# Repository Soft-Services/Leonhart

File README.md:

# Leonhart
## Overview
Leonhart is a custom embedded Linux board based on the Texas Instruments AM6231 SoC.

The board is a smart-home gateway capable of running Linux and hosting Thread and Zigbee networks simultaneously using the Silicon Labs MGM240P radio module. The goal is to provide support for Matter-over-Thread devices while also bridging Zigbee devices into modern Matter-based ecosystems such as Google Home, Amazon Alexa, and Apple Home.

## Why This Matters
Many existing smart homes rely on Zigbee devices, while newer smart-home ecosystems are increasingly moving towards Matter and Thread. Replacing Zigbee devices to keep up with Matter-based ecosystems is wasteful, expensive and unnecessary.

Leonhart was created to support both worlds at once. Hosting a Thread network for newer Matter-over-Thread devices, while also hosting a Zigbee network and allowing for communication with legacy Zigbee devices. The long-term goal is to bridge Zigbee devices into Matter-based ecosystems, allowing older devices to remain useful alongside newer smart-home standards.

## Project Goals

The main goals of Leonhart are:
- Build a fully functional custom embedded Linux system
- Run Zigbee+Thread RCP firmware on MGM240P
- Thread Border Router functionality
- Zigbee network stack to communicate with radio
- Support multi protocol through Silicon Labs CPC
- Create a compact, local and open Linux-based alternative to separate Zigbee hubs and Thread border routers

## Current Status

Rev B is currently functional. Working features include:
- Linux boot from eMMC
- Ethernet and SSH
- USB-C powered boot
- Multiprotocol firmware flashed to MGM240P
- UART communication between Linux host and MGM240P with hardware flow control
- Silicon Labs CPC daemon communication
- OpenThread Border Router operation
- Thread and Zigbee network formation
- Automatic startup of Zigbee, OTBR and CPC services
- Matter-over-Thread device control using chip-tool
- Zigbee device control through Matter chip-tool commands using a simple FIFO-based Matter bridge

### Current Demo

Leonhart currently demonstrates Matter-over-Thread control and early Zigbee-to-Matter bridge functionality using the onboard MGM240P radio.

<br>

## Hardware Architecture

### Key Features
- TI AM6231 SoC
- 2 GB DDR4
- SiLabs MGM240P RF module
- 16 GB eMMC storage (HS200)
- Ethernet (RGMII PHY)
- 32kbit EEPROM
- USB-A host port
- USB-C power input
- SoC JTAG/MGM240P SWD TagConnect debug interfaces
- SPI and UART header pins for extra peripherals

### Hardware Block Diagram

<br>

## Hardware Revisions

### Rev A

Rev A was the initial bring-up revision. It successfully validated the core AM6231 Linux system, including PMIC rail sequencing, U-Boot over UART, DDR4 initialization, eMMC HS200 operation, EEPROM communication, USB-A, clocks, and Linux boot.

Main issues found in Rev A:
- Incorrect 5 V to 3.3 V buck converter footprint, requiring external 3.3 V injection
- USB-C power issue caused by the bodged power setup
- Ethernet PHY not operational
- Linux boot on power-up affected by bodged power sequencing
- Incorrect MGM240P UART and SWD pinout

### Rev B

Rev B fixed the major hardware issues from Rev A and is the current functional revision.

Main fixes and validated features in Rev B:
- MGM240P pinout now correct and can be flashed to via Silicon Labs J-Link debugger
- Ethernet and SSH are now operational
- Correct 5V -> 3.3V buck converter footprint
- USB-C power works without bodged power supply
- Linux boots from power up
- UART communication with hardware flow control works between the AM6231 and MGM240P

## Bring-Up Notes

Progress Update #1 

During initial bring-up, a bench PSU was used and a large current draw was observed, which was then found out to be an issue with the 5V -> 3.3V buck converter footprint.

A temporary workaround involved:
- Injecting 3.3V from wall adapter into 3.3V header pin
- Using a USB-C breakout board to power the PMIC and remaining rails via a bench PSU

This allowed for successful validation of:
- SoC boot
- DDR initialization
- eMMC communication

Linux boot strategy: USB-A -> DDR -> eMMC -> DDR -> boot

Progress Update #2
- Successfully booted Linux (Arago distribution)
- Rootfs and U-Boot files copied to eMMC
- Successfully able to boot from eMMC

Progress Update #3
- Modified prebuilt ti-am625-sk.dts file with only UART pinmux (UART5) for my custom board, and build .dtb file from that, then copied it to eMMC
- Tested UART5 communication with Sparkfun Things Matter MGM240P and saw output on SOC UART terminal

Progress Update #4
- Had issue with USB C power showing incorrect voltage for 5V rail (2.2V), so I used the bench power supply for dummy power. I have found that the bodged 3.3V injection setup causes the 2.2V at the USB C VBUS pins, which prevents USB C from sending power. Without the bodged setup (correct 5V->3.3V buck converter footprint) in the next revision, USB C power should work as intended
- Created new Rev B branch and started revisions

Progress Update #5 (Rev B)
- Confirmed gigabit Ethernet works and SSH works
- Linux able to boot from power up
- Confirmed onboard MGM240P communication and flashing works
- Confirmed UART hardware flow with MGM240P works
- Need to fix NCP and RCP firmware communication with CPC daemon

Progress Update #6 (Rev B)
- Successfully flashed Multiprotocol RCP/NCP (Thread and Zigbee) stack to MGM240P and had successful communication with host CPCD
- Successfully proved full Thread network chain (RCP(MGM) <-> (CPCD <-> OTBR)(AM6231)). Needed to rebuild TI Arago Linux image with multicast routing enabled

Progress Update #7 (Rev B)
- Made all Zigbee (zigbeed, zigbee-pty-bridge, Z3Gateway), Thread (OTBR, otbr-agent) and CPCD run on reboot, and successfully confirmed services correctly restart and devices reconnect
- Successfully proved Matter-over-Thread control with ESP32C6 running a Matter light example

The ESP32 commissions onto the Thread network through Leonhart, then registers its Matter operational service through SRP, then can be controlled from chip-tool over the LAN

Next steps
- Order more Zigbee and Matter-over-Thread and stress test the multiprotocol networking
- Begin to start/look into Zigbee -> Matter bridging

The following screenshots shows a script that displays the status' of the Zigbee and Thread networks and services:

## Hardware Photos

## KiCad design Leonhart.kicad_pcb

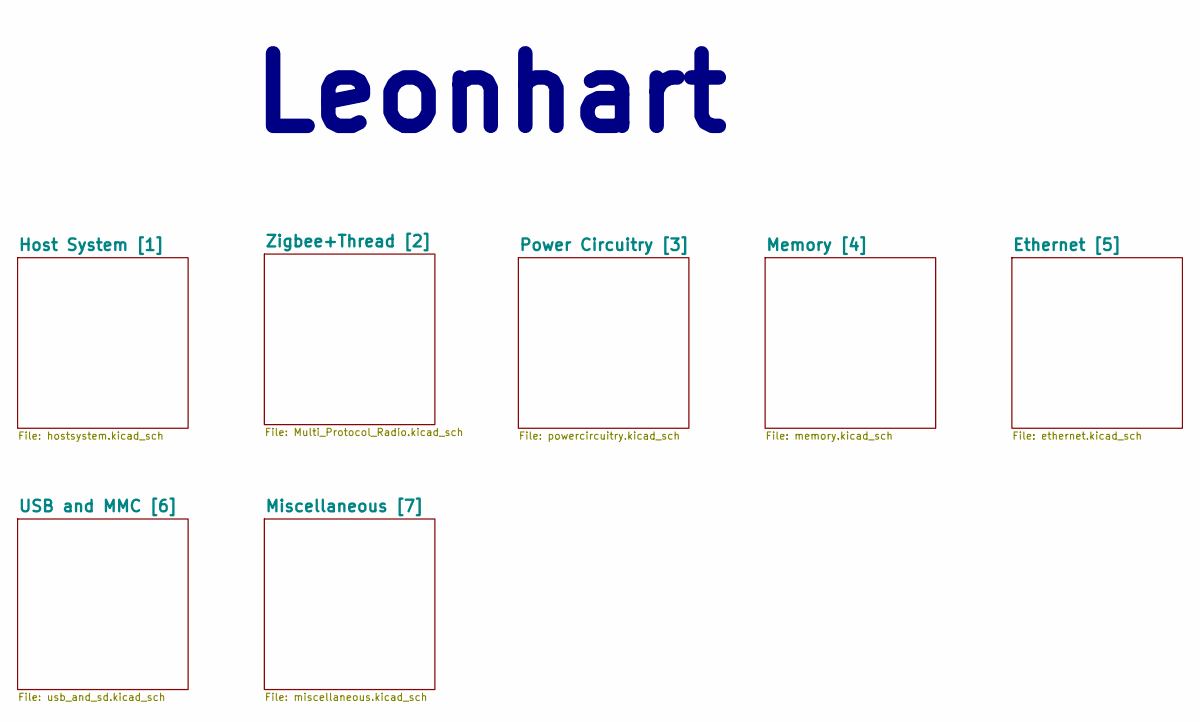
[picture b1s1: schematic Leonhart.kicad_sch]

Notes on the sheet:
Leonhart

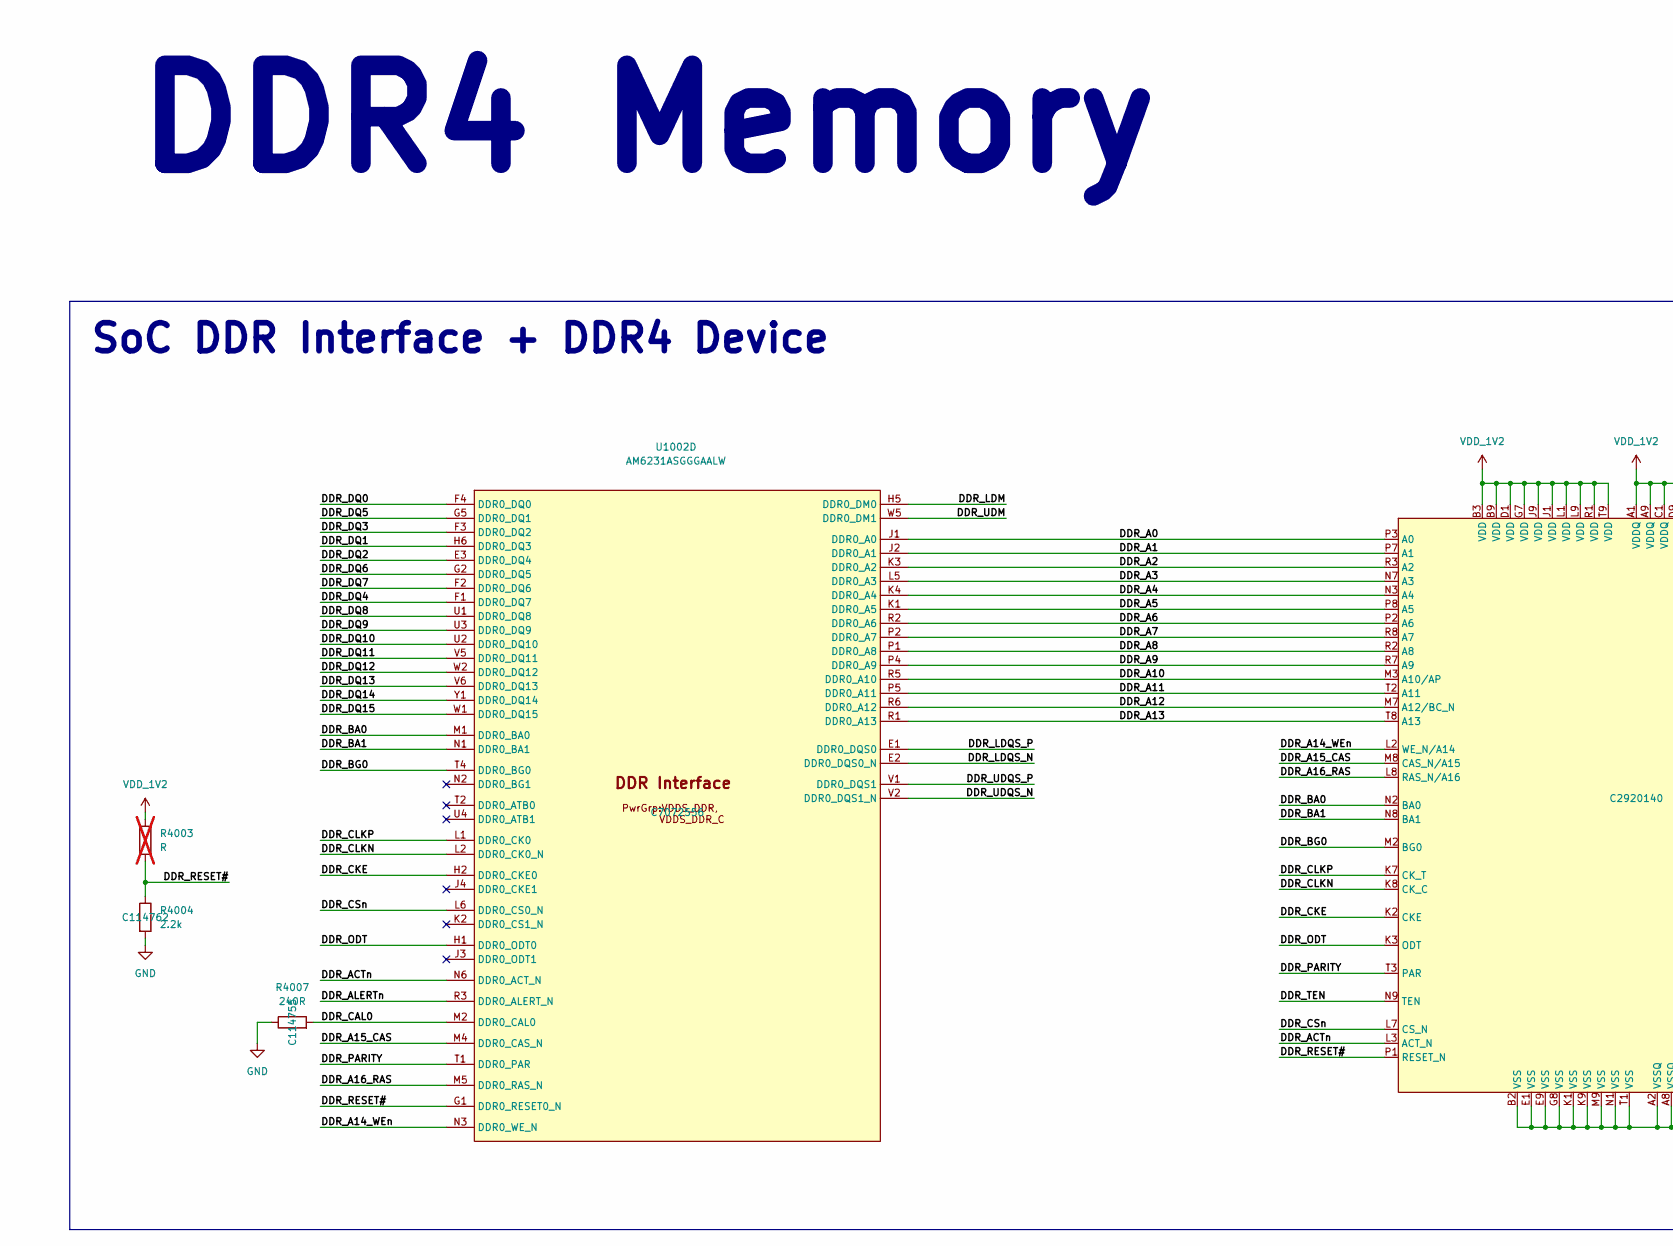
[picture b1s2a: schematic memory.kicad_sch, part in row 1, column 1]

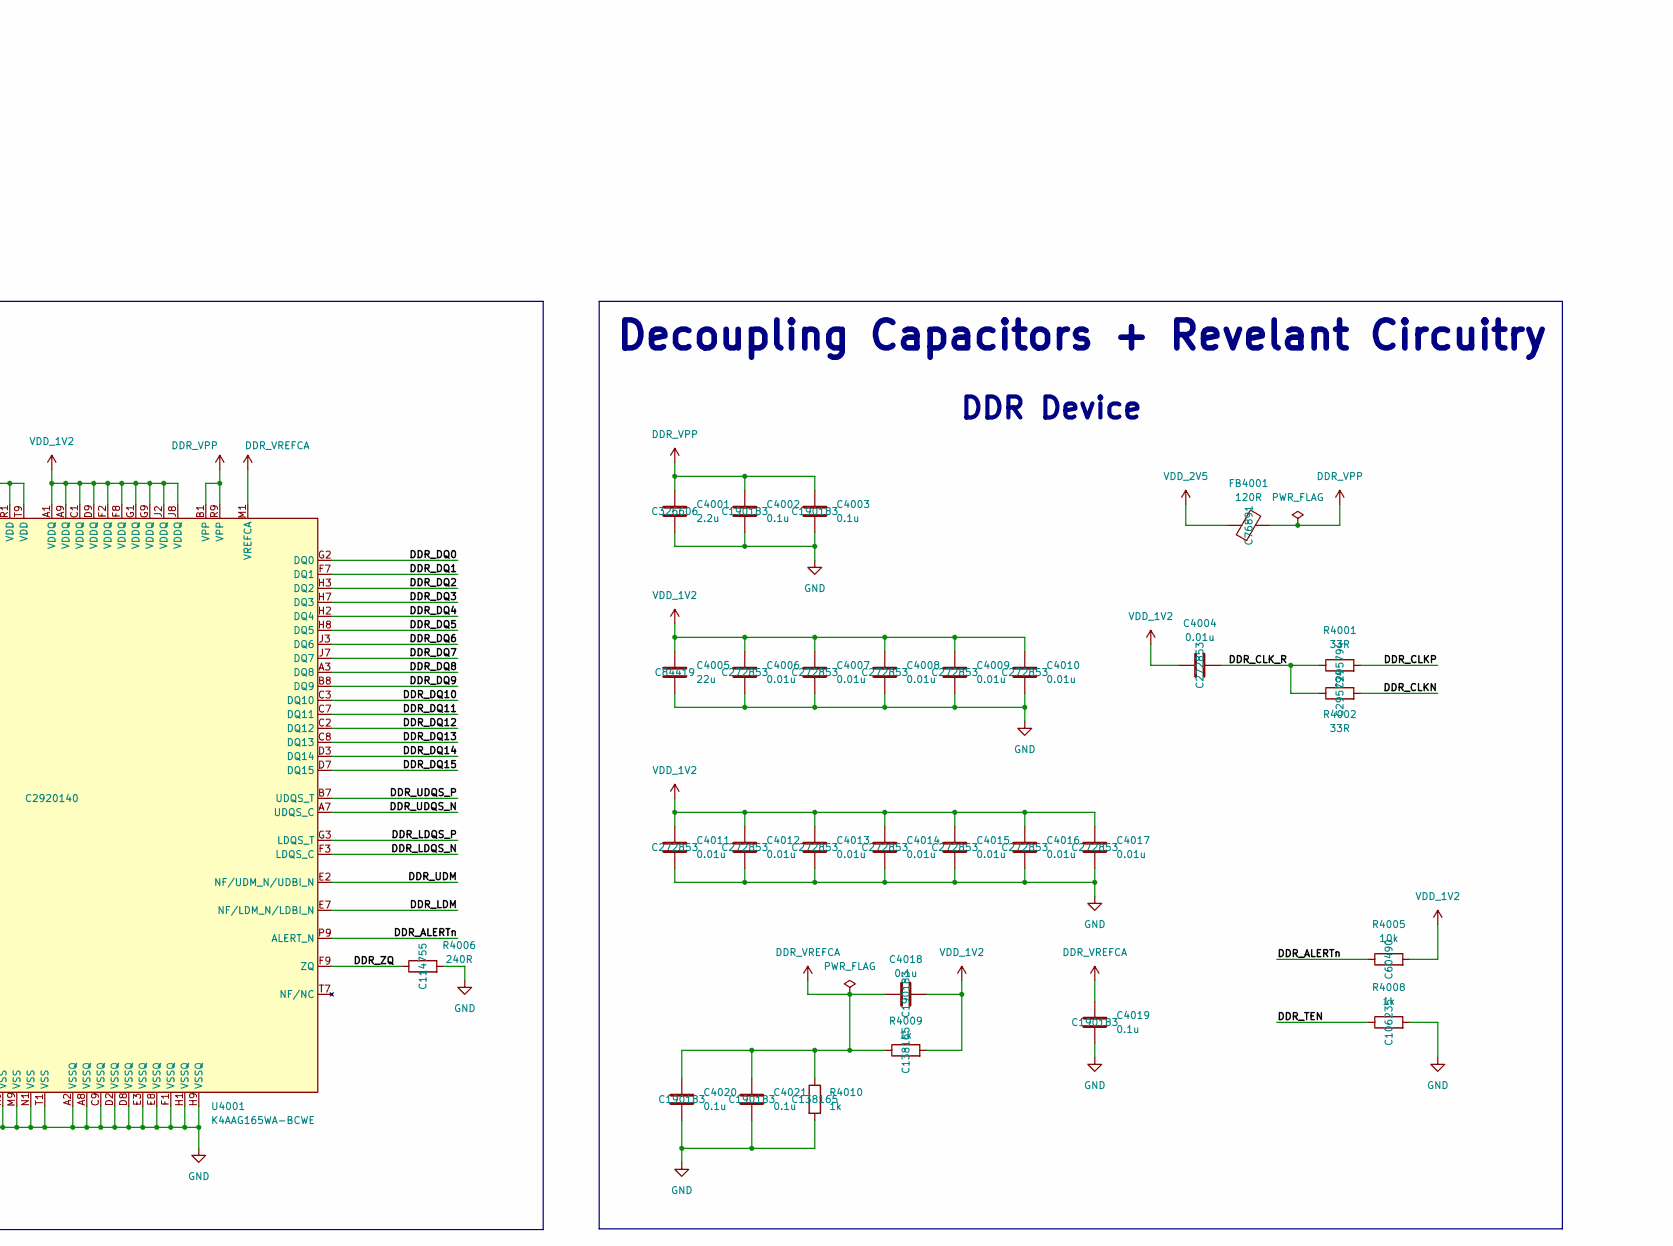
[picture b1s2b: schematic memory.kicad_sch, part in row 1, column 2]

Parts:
C4001: 2.2u; C_0402_1005Metric; JLCPCB Part# C326606
C4002, C4003, C4018, C4019, C4020, C4021: 0.1u; C_0201_0603Metric; JLCPCB Part# C190183
C4004, C4006, C4007, C4008, C4009, C4010, C4011, C4012, C4013, C4014, C4015, C4016, C4017: 0.01u; C_0201_0603Metric; JLCPCB Part# C272853
C4005: 22u; C_0603_1608Metric; JLCPCB Part# C84419
FB4001: 120R; R_0402_1005Metric; Part BLM15PX121SN1D; JLCPCB Part# C76891
R4001, R4002: 33R; R_0201_0603Metric; JLCPCB Part# C295794
R4003: R; R_0402_1005Metric; not fitted
R4004: 2.2k; R_0402_1005Metric; JLCPCB Part# C114762
R4005: 10k; R_0402_1005Metric; JLCPCB Part# C60490
R4006, R4007: 240R; R_0402_1005Metric; JLCPCB Part# C114755
R4008: 1k; R_0402_1005Metric; JLCPCB Part# C106235
R4009, R4010: 1k; R_0201_0603Metric; JLCPCB Part# C138165
U1002: AM6231ASGGGAALW; BGA425C50P25X25_1300X1300X89; JLCPCB Part# C7072556
U4001: K4AAG165WA-BCWE; FBGA-96_9x13mm_Layout9x16_P0.8mm; JLCPCB Part# C2920140

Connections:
/Memory [4]/DDR_A0: U1002.J1 (DDR0_A0), U4001.P3 (A0)
/Memory [4]/DDR_A1: U1002.J2 (DDR0_A1), U4001.P7 (A1)
/Memory [4]/DDR_A2: U1002.K3 (DDR0_A2), U4001.R3 (A2)
/Memory [4]/DDR_A3: U1002.L5 (DDR0_A3), U4001.N7 (A3)
/Memory [4]/DDR_A4: U1002.K4 (DDR0_A4), U4001.N3 (A4)
/Memory [4]/DDR_A5: U1002.K1 (DDR0_A5), U4001.P8 (A5)
/Memory [4]/DDR_A6: U1002.R2 (DDR0_A6), U4001.P2 (A6)
/Memory [4]/DDR_A7: U1002.P2 (DDR0_A7), U4001.R8 (A7)
/Memory [4]/DDR_A8: U1002.P1 (DDR0_A8), U4001.R2 (A8)
/Memory [4]/DDR_A9: U1002.P4 (DDR0_A9), U4001.R7 (A9)
/Memory [4]/DDR_A10: U1002.R5 (DDR0_A10), U4001.M3 (A10/AP)
/Memory [4]/DDR_A11: U1002.P5 (DDR0_A11), U4001.T2 (A11)
/Memory [4]/DDR_A12: U1002.R6 (DDR0_A12), U4001.M7 (A12/BC_N)
/Memory [4]/DDR_A13: U1002.R1 (DDR0_A13), U4001.T8 (A13)
/Memory [4]/DDR_A14_WEn: U1002.N3 (DDR0_WE_N), U4001.L2 (WE_N/A14)
/Memory [4]/DDR_A15_CAS: U1002.M4 (DDR0_CAS_N), U4001.M8 (CAS_N/A15)
/Memory [4]/DDR_A16_RAS: U1002.M5 (DDR0_RAS_N), U4001.L8 (RAS_N/A16)
/Memory [4]/DDR_ACTn: U1002.N6 (DDR0_ACT_N), U4001.L3 (ACT_N)
/Memory [4]/DDR_ALERTn: R4005.1, U1002.R3 (DDR0_ALERT_N), U4001.P9 (ALERT_N)
/Memory [4]/DDR_BA0: U1002.M1 (DDR0_BA0), U4001.N2 (BA0)
/Memory [4]/DDR_BA1: U1002.N1 (DDR0_BA1), U4001.N8 (BA1)
/Memory [4]/DDR_BG0: U1002.T4 (DDR0_BG0), U4001.M2 (BG0)
/Memory [4]/DDR_CAL0: R4007.2, U1002.M2 (DDR0_CAL0)
/Memory [4]/DDR_CKE: U1002.H2 (DDR0_CKE0), U4001.K2 (CKE)
/Memory [4]/DDR_CLKN: R4002.2, U1002.L2 (DDR0_CK0_N), U4001.K8 (CK_C)
/Memory [4]/DDR_CLKP: R4001.2, U1002.L1 (DDR0_CK0), U4001.K7 (CK_T)
/Memory [4]/DDR_CLK_R: C4004.2, R4001.1, R4002.1
/Memory [4]/DDR_CSn: U1002.L6 (DDR0_CS0_N), U4001.L7 (CS_N)
/Memory [4]/DDR_DQ0: U1002.F4 (DDR0_DQ0), U4001.G2 (DQ0)
/Memory [4]/DDR_DQ1: U1002.H6 (DDR0_DQ3), U4001.F7 (DQ1)
/Memory [4]/DDR_DQ2: U1002.E3 (DDR0_DQ4), U4001.H3 (DQ2)
/Memory [4]/DDR_DQ3: U1002.F3 (DDR0_DQ2), U4001.H7 (DQ3)
/Memory [4]/DDR_DQ4: U1002.F1 (DDR0_DQ7), U4001.H2 (DQ4)
/Memory [4]/DDR_DQ5: U1002.G5 (DDR0_DQ1), U4001.H8 (DQ5)
/Memory [4]/DDR_DQ6: U1002.G2 (DDR0_DQ5), U4001.J3 (DQ6)
/Memory [4]/DDR_DQ7: U1002.F2 (DDR0_DQ6), U4001.J7 (DQ7)
/Memory [4]/DDR_DQ8: U1002.U1 (DDR0_DQ8), U4001.A3 (DQ8)
/Memory [4]/DDR_DQ9: U1002.U3 (DDR0_DQ9), U4001.B8 (DQ9)
/Memory [4]/DDR_DQ10: U1002.U2 (DDR0_DQ10), U4001.C3 (DQ10)
/Memory [4]/DDR_DQ11: U1002.V5 (DDR0_DQ11), U4001.C7 (DQ11)
/Memory [4]/DDR_DQ12: U1002.W2 (DDR0_DQ12), U4001.C2 (DQ12)
/Memory [4]/DDR_DQ13: U1002.V6 (DDR0_DQ13), U4001.C8 (DQ13)
/Memory [4]/DDR_DQ14: U1002.Y1 (DDR0_DQ14), U4001.D3 (DQ14)
/Memory [4]/DDR_DQ15: U1002.W1 (DDR0_DQ15), U4001.D7 (DQ15)
/Memory [4]/DDR_LDM: U1002.H5 (DDR0_DM0), U4001.E7 (NF/LDM_N/LDBI_N)
/Memory [4]/DDR_LDQS_N: U1002.E2 (DDR0_DQS0_N), U4001.F3 (LDQS_C)
/Memory [4]/DDR_LDQS_P: U1002.E1 (DDR0_DQS0), U4001.G3 (LDQS_T)
/Memory [4]/DDR_ODT: U1002.H1 (DDR0_ODT0), U4001.K3 (ODT)
/Memory [4]/DDR_PARITY: U1002.T1 (DDR0_PAR), U4001.T3 (PAR)
/Memory [4]/DDR_RESET#: R4003.2, R4004.1, U1002.G1 (DDR0_RESET0_N), U4001.P1 (RESET_N)
/Memory [4]/DDR_TEN: R4008.1, U4001.N9 (TEN)
/Memory [4]/DDR_UDM: U1002.W5 (DDR0_DM1), U4001.E2 (NF/UDM_N/UDBI_N)
/Memory [4]/DDR_UDQS_N: U1002.V2 (DDR0_DQS1_N), U4001.A7 (UDQS_C)
/Memory [4]/DDR_UDQS_P: U1002.V1 (DDR0_DQS1), U4001.B7 (UDQS_T)
/Memory [4]/DDR_ZQ: R4006.1, U4001.F9 (ZQ)
DDR_VPP: C4001.1, C4002.1, C4003.1, FB4001.2, U4001.B1 (VPP), U4001.R9 (VPP)
DDR_VREFCA: C4018.1, C4019.1, C4020.1, C4021.1, R4009.1, R4010.1, U4001.M1 (VREFCA)
GND: C4001.2, C4002.2, C4003.2, C4005.2, C4006.2, C4007.2, C4008.2, C4009.2, C4010.2, C4011.2, C4012.2, C4013.2, C4014.2, C4015.2, C4016.2, C4017.2, C4019.2, C4020.2, C4021.2, R4004.2, R4006.2, R4007.1, R4008.2, R4010.2, U4001.A2 (VSSQ), U4001.A8 (VSSQ), U4001.B2 (VSS), U4001.C9 (VSSQ), U4001.D2 (VSSQ), U4001.D8 (VSSQ), U4001.E1 (VSS), U4001.E3 (VSSQ), U4001.E8 (VSSQ), U4001.E9 (VSS), U4001.F1 (VSSQ), U4001.G8 (VSS), U4001.H1 (VSSQ), U4001.H9 (VSSQ), U4001.K1 (VSS), U4001.K9 (VSS), U4001.M9 (VSS), U4001.N1 (VSS), U4001.T1 (VSS); also elsewhere on the board
VDD_1V2: C4004.1, C4005.1, C4006.1, C4007.1, C4008.1, C4009.1, C4010.1, C4011.1, C4012.1, C4013.1, C4014.1, C4015.1, C4016.1, C4017.1, C4018.2, R4003.1, R4005.2, R4009.2, U4001.A1 (VDDQ), U4001.A9 (VDDQ), U4001.B3 (VDD), U4001.B9 (VDD), U4001.C1 (VDDQ), U4001.D1 (VDD), U4001.D9 (VDDQ), U4001.F2 (VDDQ), U4001.F8 (VDDQ), U4001.G1 (VDDQ), U4001.G7 (VDD), U4001.G9 (VDDQ), U4001.J1 (VDD), U4001.J2 (VDDQ), U4001.J8 (VDDQ), U4001.J9 (VDD), U4001.L1 (VDD), U4001.L9 (VDD), U4001.R1 (VDD), U4001.T9 (VDD); also elsewhere on the board
VDD_2V5: FB4001.1; also elsewhere on the board

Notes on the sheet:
DDR4 Memory
SoC DDR Interface + DDR4 Device
Decoupling Capacitors + Revelant Circuitry
DDR Device
